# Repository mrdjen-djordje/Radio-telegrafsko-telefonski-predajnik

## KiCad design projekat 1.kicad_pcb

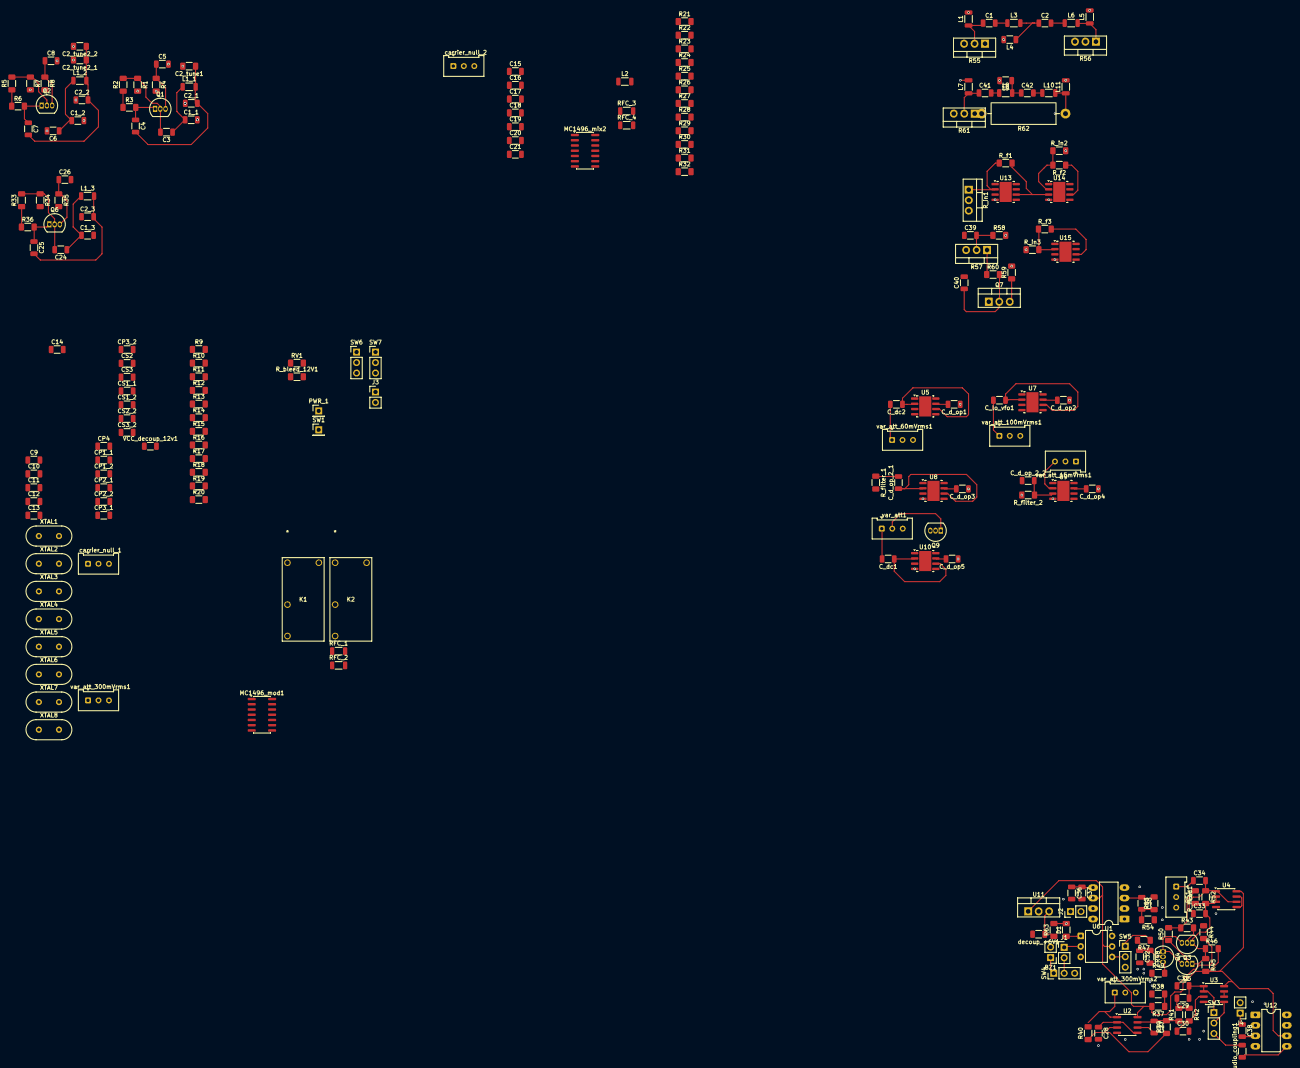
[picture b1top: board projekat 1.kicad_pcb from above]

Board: 2 copper layers, 223 parts (0 on the bottom side), 136 nets.

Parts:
BZ1: Zujalica; PinHeader_1x02_P2.54mm_Vertical
C1, C1_1, C1_3, C2, C2_2, C3, C4, C6, C7, C24, C25, C41, C42: 100p; C_1206_3216Metric
C1_2: 180p; C_1206_3216Metric
C2_1: 80p; C_1206_3216Metric
C2_3: 82p; C_1206_3216Metric
C2_tune1: 5-15p; R_1206_3216Metric_Pad1.30x1.75mm_HandSolder
C2_tune2_1, C2_tune2_2: 8-50p; R_1206_3216Metric_Pad1.30x1.75mm_HandSolder
C5, C8, C26, C31, C34, C35, C39, C40: 100n; C_1206_3216Metric
C9, C15: 10u 15V; C_1206_3216Metric
C10, C12, C13, C16, C19, C20: 0,1u; C_1206_3216Metric
C11, C14, C18, C21: 25u 15V; C_1206_3216Metric
C17: 27pF; C_1206_3216Metric
C27, C30, C33: 10n; C_1206_3216Metric
C28, C37: 100u; C_1206_3216Metric
C29, C32: 20n; C_1206_3216Metric
C36: 200n; C_1206_3216Metric
C38: 10u; C_1206_3216Metric
CP1_1, CP1_2, CP2_1, CP2_2, CP3_1, CP3_2, CP4: C; C_1206_3216Metric
CS1_1, CS1_2, CS2, CS2_2, CS3, CS3_2: C; C_1206_3216Metric
C_audio_coupling1: 10u; C_1206_3216Metric
C_d_op1, C_d_op2, C_d_op3, C_d_op4, C_d_op5: 0,1u; C_1206_3216Metric
C_d_op_2_1, C_d_op_2_2: 10n; C_1206_3216Metric
C_dc1, C_dc2: 10nF; C_1206_3216Metric
C_lo_vfo1: 10nF; C_1206_3216Metric
D1: LED; R_1206_3216Metric_Pad1.30x1.75mm_HandSolder
J1, J2, J4: Conn_01x02_Pin; PinHeader_1x02_P2.54mm_Vertical
J3: Output signal; PinHeader_1x02_P2.54mm_Vertical
K1: Relay_SPST-NO_SSB (G6B-1177C(-FD)-ND-US); RELAY_G6B-1177P-ND_OMR
K2: Relay_SPST-NO_CW (G6B-1177C(-FD)-ND-US); RELAY_G6B-1177P-ND_OMR
L1, L5, L7, L11: 1.6u; L_1206_3216Metric
L1_1, L1_2: 33uH; L_1206_3216Metric
L1_3: 10uH; L_1206_3216Metric
L2: 4,7uH; L_1206_3216Metric
L3, L6, L8, L10: 3.9u; L_1206_3216Metric
L4, L9: 750n; C_1206_3216Metric
MC1496_mix2: mixer; SOIC-14_3.9x8.7mm_P1.27mm
MC1496_mod1: modulator; SOIC-14_3.9x8.7mm_P1.27mm
PWR_1: 12Vdc; PinHeader_1x01_P2.54mm_Vertical
Q1, Q2, Q6, Q9: BC547; TO-92_Inline
Q3, Q4, Q5: BC549; TO-92_Inline
Q7: IRF510; TO-220-3_Vertical
R1, R7, R34: 5k; R_1206_3216Metric_Pad1.30x1.75mm_HandSolder
R2, R5, R33, R40: 100k; R_1206_3216Metric_Pad1.30x1.75mm_HandSolder
R3, R6, R9, R15, R21, R27, R36, R54: 1k; R_1206_3216Metric_Pad1.30x1.75mm_HandSolder
R4, R8, R10, R16, R19, R22, R28, R31, R35, R37, R38, R44, R51, R52: 10k; R_1206_3216Metric_Pad1.30x1.75mm_HandSolder
R11, R23: 3k; R_1206_3216Metric_Pad1.30x1.75mm_HandSolder
R12, R20, R24, R32: 51; R_1206_3216Metric_Pad1.30x1.75mm_HandSolder
R13, R25: 1,3k; R_1206_3216Metric_Pad1.30x1.75mm_HandSolder
R14, R26: 820; R_1206_3216Metric_Pad1.30x1.75mm_HandSolder
R17, R18, R29, R30: 100; R_1206_3216Metric_Pad1.30x1.75mm_HandSolder
R39: 47k; R_1206_3216Metric_Pad1.30x1.75mm_HandSolder
R41, R42: 33k; R_1206_3216Metric_Pad1.30x1.75mm_HandSolder
R43, R50: 330; R_1206_3216Metric_Pad1.30x1.75mm_HandSolder
R45, R46, R49: 22k; R_1206_3216Metric_Pad1.30x1.75mm_HandSolder
R47, R48: 220k; R_1206_3216Metric_Pad1.30x1.75mm_HandSolder
R53: 15k; R_1206_3216Metric_Pad1.30x1.75mm_HandSolder
R55, R56, R61: 50R; TO-220-3_Vertical
R57: R; TO-220-3_Vertical
R58, R59, R60: R; R_1206_3216Metric_Pad1.30x1.75mm_HandSolder
R62: 50R; R_Axial_DIN0516_L15.5mm_D5.0mm_P20.32mm_Horizontal
R63: 220; R_1206_3216Metric_Pad1.30x1.75mm_HandSolder
RFC_1, RFC_2, RFC_3, RFC_4: 100uH; L_1206_3216Metric
RV1: 100k; R_1206_3216Metric_Pad1.30x1.75mm_HandSolder
R_bleed_12V1: 10M; R_1206_3216Metric_Pad1.30x1.75mm_HandSolder
R_f1: 127k; R_1206_3216Metric_Pad1.30x1.75mm_HandSolder
R_f2: 3k; R_1206_3216Metric_Pad1.30x1.75mm_HandSolder
R_f3: R; R_1206_3216Metric_Pad1.30x1.75mm_HandSolder
R_filter_1, R_filter_2: R; R_1206_3216Metric_Pad1.30x1.75mm_HandSolder
R_head1: 10k_logAudio; Potentiometer_Bourns_3386W_Horizontal
R_in1: 1k; TO-220-3_Vertical
R_in2: 1k; R_1206_3216Metric_Pad1.30x1.75mm_HandSolder
R_in3: R; R_1206_3216Metric_Pad1.30x1.75mm_HandSolder
SW1: on/off_12V; PinHeader_1x01_P2.54mm_Vertical
SW3: audio_SsbMorse_selektor; PinHeader_1x03_P2.54mm_Vertical
SW4: on/off_zujanje; PinHeader_1x03_P2.54mm_Vertical
SW5: keying_CW_SSB_selektor; PinHeader_1x03_P2.54mm_Vertical
SW6: selektor_modulacija; PinHeader_1x03_P2.54mm_Vertical
SW7: selektor_izlaza; PinHeader_1x03_P2.54mm_Vertical
U1, U12: LM386; DIP-8_W7.62mm_LongPads
U2, U3, U4: LM358; SOIC-8_3.9x4.9mm_P1.27mm
U5, U7, U8, U9, U10, U13, U14, U15: OPA656UB; SOIC-8-1EP_3.9x4.9mm_P1.27mm_EP2.95x4.9mm_Mask2.34x2.34mm
U6: 4N35; DIP-6_W7.62mm
U11: L7806; TO-220-3_Vertical
VCC_decoup_12v1: 100n; C_1206_3216Metric
XTAL1, XTAL2, XTAL3, XTAL4, XTAL5, XTAL6, XTAL7, XTAL8: 4MHz; Crystal_HC49-U_Vertical
carrier_null_1, carrier_null_2: 50k; Potentiometer_Bourns_3386W_Horizontal
decoup_+6V1: 100n; C_1206_3216Metric
var_att1: 1k linear pot; Potentiometer_Bourns_3386W_Horizontal
var_att_15mVrms1, var_att_60mVrms1, var_att_100mVrms1, var_att_300mVrms1: 1k linear pot; Potentiometer_Bourns_3386W_Horizontal
var_att_300mVrms2: 100k linear pot; Potentiometer_Bourns_3386W_Horizontal

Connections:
+6V: R43.1, R50.2, R51.2, R63.1, U11.3 (OUT), decoup_+6V1.1
/1: C9.1, MC1496_mod1.1, R16.1, R17.1
/1_2: C15.1, MC1496_mix2.1, R28.1, R29.1
/1k_820_junction: R14.2, R15.1, R17.2, R18.1
/1k_820_junction_2: R26.2, R27.1, R29.2, R30.1
/2nd_ampl: C39.1, R_f2.1, R_f3.2, U14.6 (OUTPUT), U15.6 (OUTPUT)
/4: C14.1, MC1496_mod1.4, R18.2, R19.1, R20.1
/4_2: C21.1, MC1496_mix2.4, R30.2, R31.1, R32.1
/7MHz_unBuff: C2_3.2, C25.2, L1_3.2, U10.3 (POS)
/12V_supply_1: C_d_op1.2, C_d_op2.2, C_d_op3.2, C_d_op4.2, R2.1, R3.1, R5.1, R6.1, R10.1, R11.1, R13.1, R22.1, R23.1, R25.1, R37.2, R45.2, R46.2, RFC_1.2, RFC_2.1, RFC_3.1, RFC_4.2, SW6.1 (A), U1.6 (V+), U2.8 (V+), U3.8 (V+), U4.8 (V+), U5.7 (+VS), U6.5, U7.7 (+VS), U8.7 (+VS), U9.7 (+VS), U11.1 (IN), U12.6 (V+)
/12V_supply_CW: C_d_op5.2, R33.1, R36.1, SW6.3 (C), U10.7 (+VS)
/14: C14.2, MC1496_mod1.14
/14_2: C21.2, MC1496_mix2.14
/LO_VFO: C19.1, var_att_100mVrms1.2
/buff_01: C2_1.2, C2_tune1.1, C4.2, L1_1.2, U5.3 (POS)
/buff_02: C2_2.2, C2_tune2_1.1, C2_tune2_2.1, C7.2, L1_2.2, U7.3 (POS)
/buff_03: C10.2, U8.3 (POS)
/carrier: C12.1, var_att_60mVrms1.2
/dsb_sc: CS1_1.1, R_filter_1.2
/keying: Q9.2 (B), SW5.3 (C)
/output: C40.2, J3.1
/output_7MHz_SSB: C17.1, L2.2
/output_amplification_cw: L10.2, L11.1, R62.1, U15.3 (POS)
/output_amplification_ssb: L5.1, L6.2, R56.1, U13.3 (POS)
/signal: U3.6 (-), U3.7, var_att_300mVrms1.3
/ssb: C15.2, var_att_15mVrms1.2
/ssb_unBuff: CS1_2.2, C_d_op_2_2.1
GND: BZ1.2 (-), C1_1.2, C1_2.2, C1_3.2, C2_1.1, C2_2.1, C2_3.1, C2_tune1.2, C2_tune2_1.2, C2_tune2_2.2, C5.2, C8.2, C11.1, C13.1, C17.2, C18.1, C20.1, C26.2, C28.2, C30.2, C32.2, C36.2, CP1_1.2, CP1_2.2, CP2_1.2, CP2_2.2, CP3_1.2, CP3_2.2, CP4.2, C_d_op1.1, C_d_op2.1, C_d_op3.1, C_d_op4.1, C_d_op5.1, J2.1, J3.2, J4.2, L1.2, L4.2, L5.2, L7.2, L9.2, L11.2, PWR_1.1 (Pin_1_1), R1.2, R4.2, R7.2, R8.2, R15.2, R20.2, R27.2, R32.2, R34.2, R35.2, R38.1, R48.2, R49.1, R54.1, R56.2, R58.2, R59.2, R62.2, R_bleed_12V1.2, R_filter_2.2, R_head1.3, R_in1.2, R_in2.2, R_in3.1, SW4.3 (C), U1.2 (-), U1.4 (GND), U2.4 (V-), U3.4 (V-), U4.4 (V-), U5.4 (-VS), U7.4 (-VS), U8.4 (-VS), U9.4 (-VS), U10.4 (-VS), U11.2 (GND), U12.2 (-), U12.4 (GND), U13.4 (-VS), U14.4 (-VS), U15.4 (-VS), VCC_decoup_12v1.2, carrier_null_1.2, carrier_null_2.2, decoup_+6V1.2, var_att1.3, var_att_15mVrms1.1, var_att_60mVrms1.3, var_att_100mVrms1.3, var_att_300mVrms1.1, var_att_300mVrms2.3
unnamed: BZ1.1 (+), SW4.1 (A)
unnamed: C1.1, L1.1, R55.2
unnamed: C1.2, L3.1
unnamed: C1_1.1, C3.1, L1_1.1
unnamed: C1_2.1, C6.1, L1_2.1
unnamed: C1_3.1, C24.1, L1_3.1
unnamed: C2.1, L3.2, L4.1
unnamed: C2.2, L6.1
unnamed: C9.2, var_att_300mVrms1.2
unnamed: C10.1, MC1496_mod1.6, R11.2, RFC_2.2
unnamed: C11.2, C13.2, MC1496_mod1.8, R12.1, R13.2, R14.1
unnamed: C12.2, MC1496_mod1.10, R12.2
unnamed: C16.1, MC1496_mix2.6, R23.2, RFC_3.2
unnamed: C16.2, L2.1
unnamed: C18.2, C20.2, MC1496_mix2.8, R24.1, R25.2, R26.1
unnamed: C19.2, MC1496_mix2.10, R24.2
unnamed: C27.1, R39.2, R41.1, U2.7
unnamed: C29.2, R41.2, R42.1
unnamed: C31.1, R44.2
unnamed: C34.1, R_head1.1
unnamed: C35.2, R53.1, R54.2
unnamed: C36.1, C37.1, U1.5
unnamed: C41.1, L7.1, R61.2
unnamed: C41.2, L8.1
unnamed: C42.1, L8.2, L9.1
unnamed: C42.2, L10.1
unnamed: CP1_1.1, XTAL1.2, XTAL2.1
unnamed: CP1_2.1, XTAL7.2, XTAL8.1
unnamed: CP2_1.1, XTAL2.2, XTAL3.1
unnamed: CP2_2.1, XTAL6.2, XTAL7.1
unnamed: CP3_1.1, CS2.2, XTAL4.1
unnamed: CP3_2.1, CS2_2.1, XTAL5.2
unnamed: CP4.1, CS3.2, CS3_2.1
unnamed: CS1_1.2, XTAL1.1
unnamed: CS1_2.1, XTAL8.2
unnamed: CS2.1, XTAL3.2
unnamed: CS2_2.2, XTAL6.1
unnamed: CS3.1, XTAL4.2
unnamed: CS3_2.2, XTAL5.1
unnamed: C_audio_coupling1.1, U12.5
unnamed: C_d_op_2_1.2, R_filter_1.1
unnamed: C_dc1.2, var_att1.1
unnamed: C_dc2.2, var_att_60mVrms1.1
unnamed: C_lo_vfo1.2, var_att_100mVrms1.1
unnamed: D1.2 (A), R63.2
unnamed: D1.1 (K), U6.1
unnamed: J1.1, U6.2
unnamed: J1.2, SW4.2 (B)
unnamed: C37.2, J2.2
unnamed: C38.1, J4.1
unnamed: MC1496_mix2.2, R21.2
unnamed: MC1496_mix2.3, R21.1
unnamed: MC1496_mix2.5, R22.2
unnamed: MC1496_mix2.12, RFC_4.1
unnamed: MC1496_mod1.2, R9.2
unnamed: MC1496_mod1.3, R9.1
unnamed: MC1496_mod1.5, R10.2
unnamed: MC1496_mod1.12, RFC_1.1
unnamed: C3.2, Q1.2 (B), R1.1, R2.2
unnamed: C4.1, Q1.1 (C), R3.2
unnamed: C5.1, Q1.3 (E), R4.1
unnamed: C6.2, Q2.2 (B), R5.2, R7.1
unnamed: C7.1, Q2.1 (C), R6.2
unnamed: C8.1, Q2.3 (E), R8.1
unnamed: Q3.2 (B), R43.2, R44.1
unnamed: C33.2, Q3.1 (C), Q5.1 (C), R45.1, R46.1, R51.1, R52.2, U4.2 (-), U4.3 (+)
unnamed: Q3.3 (E), Q4.1 (C), Q5.3 (E)
unnamed: C32.1, Q4.2 (B), R47.2, R48.1
unnamed: Q4.3 (E), R49.2
unnamed: Q5.2 (B), R50.1
unnamed: C24.2, Q6.2 (B), R33.2, R34.1
unnamed: C25.1, Q6.1 (C), R36.2
unnamed: C26.1, Q6.3 (E), R35.1
unnamed: C40.1, Q7.2 (D), R60.2
unnamed: C39.2, Q7.1 (G), R57.2, R58.1
unnamed: Q7.3 (S), R59.1
unnamed: Q9.1 (C), var_att1.2
unnamed: R16.2, carrier_null_1.3
unnamed: R19.2, carrier_null_1.1
unnamed: R28.2, carrier_null_2.3
unnamed: R31.2, carrier_null_2.1
unnamed: R37.1, R38.2
unnamed: R40.2, RV1.1, U2.1, var_att_300mVrms2.1
unnamed: R53.2, R_head1.2
unnamed: C29.1, C31.2, SW3.1 (A), U3.1, U3.2 (-)
unnamed: SW3.2 (B), U3.5 (+)
unnamed: C_audio_coupling1.2, SW3.3 (C)
unnamed: R47.1, SW5.1 (A)
unnamed: SW5.2 (B), U6.4
unnamed: C35.1, U1.3 (+)
unnamed: R39.1, R40.1, U2.3 (+)
unnamed: C28.1, U2.2 (-), U2.5 (+)
unnamed: C27.2, RV1.2, U2.6 (-), var_att_300mVrms2.2
unnamed: C30.1, R42.2, U3.3 (+)
unnamed: U4.5 (+), U4.7
unnamed: C33.1, C34.2, R52.1, U4.1, U4.6 (-)
unnamed: C_dc2.1, U5.2 (NEG), U5.6 (OUTPUT)
unnamed: C_lo_vfo1.1, U7.2 (NEG), U7.6 (OUTPUT)
unnamed: C_d_op_2_1.1, U8.2 (NEG), U8.6 (OUTPUT)
unnamed: U9.2 (NEG), U9.6 (OUTPUT), var_att_15mVrms1.3
unnamed: C_d_op_2_2.2, R_filter_2.1, U9.3 (POS)
unnamed: C_dc1.1, U10.2 (NEG), U10.6 (OUTPUT)
unnamed: C38.2, U12.3 (+)
unnamed: R_f1.1, R_in1.1, U13.2 (NEG)
unnamed: R_f1.2, U13.6 (OUTPUT), U14.3 (POS)
unnamed: R_f2.2, R_in2.1, U14.2 (NEG)
unnamed: R_f3.1, R_in3.2, U15.2 (NEG)
VCC: R57.1, R60.1, R_bleed_12V1.1, SW6.2 (B), SW7.2 (B), U13.7 (+VS), U14.7 (+VS), U15.7 (+VS), VCC_decoup_12v1.1
